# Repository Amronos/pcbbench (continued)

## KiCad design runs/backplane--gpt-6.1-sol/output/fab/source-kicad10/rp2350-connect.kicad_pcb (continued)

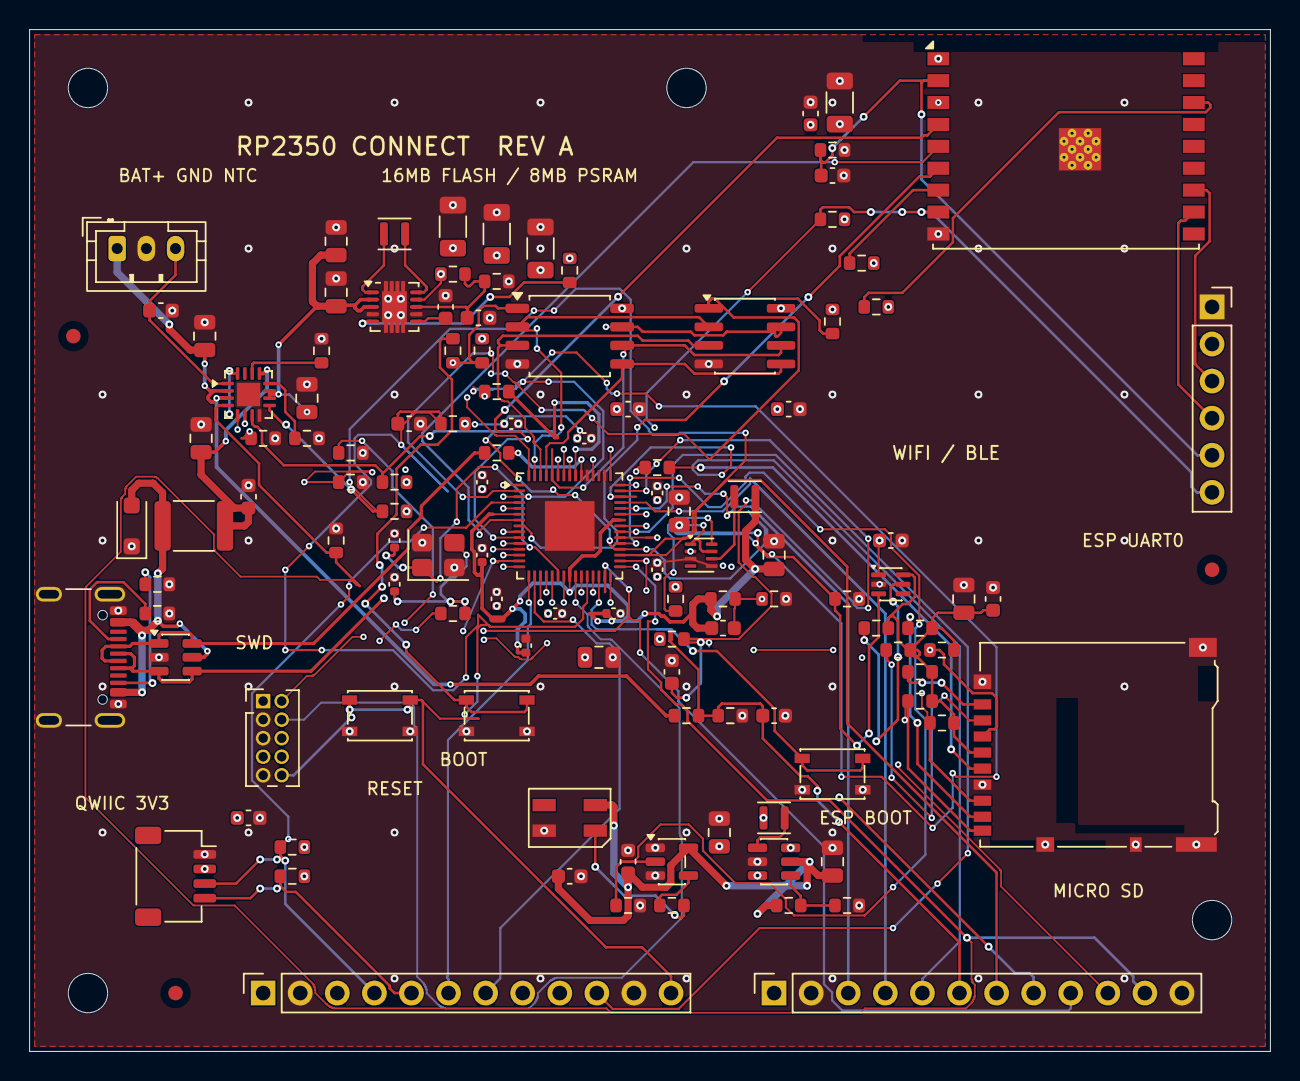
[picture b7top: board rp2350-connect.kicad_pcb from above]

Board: 6 copper layers, 85.0 x 70.0 mm, 125 parts (0 on the bottom side), 83 nets.

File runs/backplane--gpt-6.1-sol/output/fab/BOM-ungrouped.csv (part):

Reference,Value,Manufacturer,Manufacturer part number,Footprint,Fit,Notes
U1,RP2350A,Raspberry Pi,RP2350A,connect:QFN-60-1EP_7x7mm_P0.4mm_EP3.4x3.4mm,YES,Procure A2 or later silicon; do not substitute A1. Externally supplied 1.1V core; firmware sets VREG.HIZ.
U2,16MB QSPI,Winbond,W25Q128JVSIQ,connect:SOIC-8_5.3x5.3mm_P1.27mm,YES,
U3,8MB PSRAM,AP Memory,APS6404L-3SQR-SN,connect:SOIC-8_3.9x4.9mm_P1.27mm,YES,
R1,10k,Yageo,RC0603FR-0710KL,connect:R_0603_1608Metric,YES,
R2,10k,Yageo,RC0603FR-0710KL,connect:R_0603_1608Metric,YES,
C1,100n,Murata,GRM188R71C104KA01D,connect:C_0603_1608Metric,YES,
C2,100n,Murata,GRM188R71C104KA01D,connect:C_0603_1608Metric,YES,
U4,1.1V core buck,Texas Instruments,TPS62823DLCR,connect:Texas_VSON-HR-8_1.5x2mm_P0.5mm,YES,
L1,470nH,Murata,DFE201610P-R47M=P2,connect:L_Murata_DFE201610P,YES,
C3,4.7u,Murata,GRM21BR61A475KA73L,connect:C_0805_2012Metric,YES,
C4,10u,Murata,GRM21BR61A106KE19L,connect:C_0805_2012Metric,YES,
R3,83.5k,Yageo,RC0603FR-0783K5L,connect:R_0603_1608Metric,YES,
R4,100k,Yageo,RC0603FR-07100KL,connect:R_0603_1608Metric,YES,
C5,120p,Murata,GRM1885C1H121JA01D,connect:C_0603_1608Metric,YES,
R5,100k,Yageo,RC0603FR-07100KL,connect:R_0603_1608Metric,YES,
C6,100n,Murata,GRM155R71C104KA88D,connect:C_0402_1005Metric,YES,
C7,100n,Murata,GRM155R71C104KA88D,connect:C_0402_1005Metric,YES,
C8,100n,Murata,GRM155R71C104KA88D,connect:C_0402_1005Metric,YES,
C9,100n,Murata,GRM155R71C104KA88D,connect:C_0402_1005Metric,YES,
C10,100n,Murata,GRM155R71C104KA88D,connect:C_0402_1005Metric,YES,
C11,100n,Murata,GRM155R71C104KA88D,connect:C_0402_1005Metric,YES,
C12,100n,Murata,GRM155R71C104KA88D,connect:C_0402_1005Metric,YES,
C13,100n,Murata,GRM155R71C104KA88D,connect:C_0402_1005Metric,YES,
C14,100n,Murata,GRM155R71C104KA88D,connect:C_0402_1005Metric,YES,
C15,100n,Murata,GRM155R71C104KA88D,connect:C_0402_1005Metric,YES,
C16,4.7u,Murata,GRM21BR61A475KA73L,connect:C_0805_2012Metric,YES,
C17,1u,Murata,GRM188R61C105KA93D,connect:C_0603_1608Metric,YES,
R6,200,Yageo,RC0603FR-07200RL,connect:R_0603_1608Metric,YES,
Y1,12MHz CL10pF,Abracon,ABM8-272-T3,connect:Crystal_SMD_3225-4Pin_3.2x2.5mm,YES,"12MHz, CL=10pF, ESR <=50 ohms."
R7,1k,Yageo,RC0603FR-071KL,connect:R_0603_1608Metric,YES,
C18,15p,Murata,GRM1555C1H150JA01D,connect:C_0402_1005Metric,YES,
C19,15p,Murata,GRM1555C1H150JA01D,connect:C_0402_1005Metric,YES,
R8,10k,Yageo,RC0603FR-0710KL,connect:R_0603_1608Metric,YES,
C20,100n,Murata,GRM188R71C104KA01D,connect:C_0603_1608Metric,YES,
SW1,Pushbutton,C&K,PTS810SJM250SMTRLFS,connect:SW_SPST_PTS810,YES,
R9,1k,Yageo,RC0603FR-071KL,connect:R_0603_1608Metric,YES,
SW2,Pushbutton,C&K,PTS810SJM250SMTRLFS,connect:SW_SPST_PTS810,YES,
J1,USB-C,GCT,USB4105-GF-A,connect:USB_C_Receptacle_GCT_USB4105-xx-A_16P_TopMnt_Horizontal,YES,
R10,5.1k,Yageo,RC0603FR-075K1L,connect:R_0603_1608Metric,YES,
R11,5.1k,Yageo,RC0603FR-075K1L,connect:R_0603_1608Metric,YES,
U5,USB ESD,STMicroelectronics,USBLC6-2SC6,connect:SOT-23-6,YES,
R12,27,Yageo,RC0603FR-0727RL,connect:R_0603_1608Metric,YES,
R13,27,Yageo,RC0603FR-0727RL,connect:R_0603_1608Metric,YES,
F1,750mA resettable,Bourns,MF-MSMF075-2,connect:Fuse_1812_4532Metric,YES,
D1,5V TVS,Littelfuse,SMF5.0A,connect:D_SOD-123F,YES,
C21,1u,Murata,GRM188R61C105KA93D,connect:C_0603_1608Metric,YES,
U6,LiPo power-path,Texas Instruments,BQ24074RGTR,connect:VQFN-16-1EP_3x3mm_P0.5mm_EP1.6x1.6mm,YES,"External protected 1S 4.2V pack with 10k NTC. ISET=1.78k, nominal499mA. ITERM default10%."
J2,LiPo + NTC,JST,B3B-PH-K-S(LF)(SN),connect:JST_PH_B3B-PH-K_1x03_P2.00mm_Vertical,YES,
C22,10u,Murata,GRM21BR61A106KE19L,connect:C_0805_2012Metric,YES,
C23,10u,Murata,GRM21BR61A106KE19L,connect:C_0805_2012Metric,YES,
C24,10u,Murata,GRM21BR61A106KE19L,connect:C_0805_2012Metric,YES,
R14,1.78k,Yageo,RC0603FR-071K78L,connect:R_0603_1608Metric,YES,
R15,3.24k,Yageo,RC0603FR-073K24L,connect:R_0603_1608Metric,YES,
R16,39k,Yageo,RC0603FR-0739KL,connect:R_0603_1608Metric,YES,
R17,100k,Yageo,RC0603FR-07100KL,connect:R_0603_1608Metric,YES,
R18,100k,Yageo,RC0603FR-07100KL,connect:R_0603_1608Metric,YES,
R19,100k,Yageo,RC0603FR-07100KL,connect:R_0603_1608Metric,YES,
R20,10k,Yageo,RC0603FR-0710KL,connect:R_0603_1608Metric,YES,
R21,10k,Yageo,RC0603FR-0710KL,connect:R_0603_1608Metric,YES,
C25,100n,Murata,GRM188R71C104KA01D,connect:C_0603_1608Metric,YES,
U7,3.3V buck-boost,Texas Instruments,TPS63060DSCR,connect:Texas_S-PWSON-N10,YES,
L2,1uH,Murata,DFE201610P-1R0M=P2,connect:L_Murata_DFE201610P,YES,
C26,10u,Murata,GRM21BR61A106KE19L,connect:C_0805_2012Metric,YES,
C27,10u,Murata,GRM21BR61A106KE19L,connect:C_0805_2012Metric,YES,
C28,22u,Murata,GRM31CR61A226KE19L,connect:C_1206_3216Metric,YES,
C29,22u,Murata,GRM31CR61A226KE19L,connect:C_1206_3216Metric,YES,
C30,22u,Murata,GRM31CR61A226KE19L,connect:C_1206_3216Metric,YES,
C31,100n,Murata,GRM188R71C104KA01D,connect:C_0603_1608Metric,YES,
R22,560k,Yageo,RC0603FR-07560KL,connect:R_0603_1608Metric,YES,
R23,100k,Yageo,RC0603FR-07100KL,connect:R_0603_1608Metric,YES,
C32,10p,Murata,GRM1885C1H100JA01D,connect:C_0603_1608Metric,YES,
R24,100k,Yageo,RC0603FR-07100KL,connect:R_0603_1608Metric,YES,
R25,100k,Yageo,RC0603FR-07100KL,connect:R_0603_1608Metric,YES,
R26,100k,Yageo,RC0603FR-07100KL,connect:R_0603_1608Metric,YES,
C33,100n,Murata,GRM188R71C104KA01D,connect:C_0603_1608Metric,YES,
U8,Wi-Fi + BLE,Espressif Systems,ESP32-C3-WROOM-02-N4,connect:ESP32-C3-WROOM-02,YES,4MB module. Antenna projects beyond PCB north edge. Load ESP32-C3-WROOM-02 ESP-AT binary on UART0; command UART1 is GPIO6/7/5/4.
C34,22u,Murata,GRM31CR61A226KE19L,connect:C_1206_3216Metric,YES,
C35,100n,Murata,GRM188R71C104KA01D,connect:C_0603_1608Metric,YES,
R27,10k,Yageo,RC0603FR-0710KL,connect:R_0603_1608Metric,YES,
C36,100n,Murata,GRM188R71C104KA01D,connect:C_0603_1608Metric,YES,
R28,10k,Yageo,RC0603FR-0710KL,connect:R_0603_1608Metric,YES,
R29,10k,Yageo,RC0603FR-0710KL,connect:R_0603_1608Metric,YES,
R30,10k,Yageo,RC0603FR-0710KL,connect:R_0603_1608Metric,YES,
SW3,Pushbutton,C&K,PTS810SJM250SMTRLFS,connect:SW_SPST_PTS810,YES,
J3,ESP UART0,Samtec,SSQ-106-03-G-S,connect:PinSocket_1x06_P2.54mm_Vertical,YES,
J4,microSD SPI,Hirose,DM3AT-SF-PEJM5,connect:microSD_HC_Hirose_DM3AT-SF-PEJM5,YES,
R31,47k,Yageo,RC0603FR-0747KL,connect:R_0603_1608Metric,YES,
R32,47k,Yageo,RC0603FR-0747KL,connect:R_0603_1608Metric,YES,
R33,47k,Yageo,RC0603FR-0747KL,connect:R_0603_1608Metric,YES,
R34,47k,Yageo,RC0603FR-0747KL,connect:R_0603_1608Metric,YES,
R35,47k,Yageo,RC0603FR-0747KL,connect:R_0603_1608Metric,YES,
R36,47k,Yageo,RC0603FR-0747KL,connect:R_0603_1608Metric,YES,
R37,33,Yageo,RC0603FR-0733RL,connect:R_0603_1608Metric,YES,
C37,10u,Murata,GRM21BR61A106KE19L,connect:C_0805_2012Metric,YES,
C38,100n,Murata,GRM188R71C104KA01D,connect:C_0603_1608Metric,YES,
J5,Qwiic / STEMMA QT,JST,SM04B-SRSS-TB(LF)(SN),connect:JST_SH_SM04B-SRSS-TB_1x04-1MP_P1.00mm_Horizontal,YES,
R38,4.7k,Yageo,RC0603FR-074K7L,connect:R_0603_1608Metric,YES,
R39,4.7k,Yageo,RC0603FR-074K7L,connect:R_0603_1608Metric,YES,
C39,100n,Murata,GRM188R71C104KA01D,connect:C_0603_1608Metric,YES,
U9,5V LED boost,Microchip,MCP1640T-I/CHY,connect:SOT-23-6_LED,YES,
L3,2.2uH,Murata,DFE201610P-2R2M=P2,connect:L_Murata_DFE201610P,YES,
C40,4.7u,Murata,GRM21BR61A475KA73L,connect:C_0805_2012Metric,YES,
C41,10u,Murata,GRM21BR61A106KE19L,connect:C_0805_2012Metric,YES,
R40,976k,Yageo,RC0603FR-07976KL,connect:R_0603_1608Metric,YES,
R41,309k,Yageo,RC0603FR-07309KL,connect:R_0603_1608Metric,YES,
U10,LED level buffer,Texas Instruments,SN74AHCT1G125DBVR,connect:SOT-23-5,YES,
C42,100n,Murata,GRM188R71C104KA01D,connect:C_0603_1608Metric,YES,
R42,330,Yageo,RC0603FR-07330RL,connect:R_0603_1608Metric,YES,
R43,100k,Yageo,RC0603FR-07100KL,connect:R_0603_1608Metric,YES,
D2,Addressable RGB,OPSCO Optoelectronics,SK6812MINI,connect:LED_SK6812MINI_PLCC4_3.5x3.5mm_P1.75mm,YES,"5V supply, GRB data at800kHz; recommended brightness/current cap in firmware."
C43,100n,Murata,GRM188R71C104KA01D,connect:C_0603_1608Metric,YES,
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
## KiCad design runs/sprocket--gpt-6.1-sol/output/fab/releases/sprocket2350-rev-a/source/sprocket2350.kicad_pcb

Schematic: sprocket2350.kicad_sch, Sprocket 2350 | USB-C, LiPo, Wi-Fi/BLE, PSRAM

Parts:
C1, C2, C9, C10, C11, C12, C13, C14, C15, C16, C17, C18, C19, C25, C28, C31, C34, C35: 100 nF; C_0603_1608Metric; MPN GRM188R71C104KA01D
C3, C4: 15 pF; C_0603_1608Metric; MPN GRM1885C1H150JA01D
C5, C7, C8: 4.7 µF; C_0805_2012Metric; MPN GRM21BR71A475KA73L
C6: 22 µF; C_0603_1608Metric; MPN GRM188R61A226ME15D
C20: 100 nF; C_0201_0603Metric; MPN GRM033Z71C104KE14D
C21, C29: 1 µF; C_0603_1608Metric; MPN GRM188R71C105KA12D
C22, C23, C24, C30, C33: 10 µF; C_0805_2012Metric; MPN GRM21BC71E106ME11L
C26, C27, C32: 22 µF; C_1206_3216Metric; MPN GRM31CR61A226KE19L
D1: RGB V6; LED_WS2812B_PLCC4_5.0x5.0mm_P3.2mm; MPN WS2812B-V6
FID1, FID2, FID3: Fiducial; Fiducial_1mm_Mask2mm; MPN COPPER-FIDUCIAL
H1, H2, H3: M2.5; MountingHole_2.7mm_M2.5; MPN NPTH-2.7MM
J1: USB-C; USB_C_Receptacle_GCT_USB4105-xx-A_16P_TopMnt_Horizontal; MPN USB4105-GF-A
J2: LiPo; JST_PH_S2B-PH-SM4-TB_1x02-1MP_P2.00mm_Horizontal; MPN S2B-PH-SM4-TB(LF)(SN)
J3: Radio UART; PinHeader_1x04_P2.54mm_Vertical; MPN TSW-104-07-G-S
J4: microSD; microSD_HC_Hirose_DM3AT-SF-PEJM5; MPN DM3AT-SF-PEJM5
J5: Qwiic / STEMMA QT; JST_SH_BM04B-SRSS-TB_1x04-1MP_P1.00mm_Vertical; MPN BM04B-SRSS-TB(LF)(SN)
J6: GPIO; PinHeader_2x10_P2.54mm_Vertical; MPN TSW-110-07-G-D
J7: SWD; PinHeader_1x04_P2.54mm_Vertical; MPN TSW-104-07-G-S
L1: 3.3 µH; L_Abracon_AOTA-B201610S; MPN AOTA-B201610S3R3-101-T
L2: 2.2 µH; L_Coilcraft_XxL4020; MPN XFL4020-222MEC
R1, R4, R13, R16, R17, R18, R19, R23, R24, R25, R26, R27, R28, R29, R30, R31: 10 kΩ; R_0603_1608Metric; MPN RC0603FR-0710KL
R2: 1.8 kΩ; R_0603_1608Metric; MPN RC0603FR-071K8L
R3, R5, R35: 1 kΩ; R_0603_1608Metric; MPN RC0603FR-071KL
R6: 33 Ω; R_0603_1608Metric; MPN RC0603FR-0733RL
R7, R8, R32, R33: 5.1 kΩ; R_0603_1608Metric; MPN RC0603FR-075K1L
R9, R10: 27 Ω; R_0603_1608Metric; MPN RC0603FR-0727RL
R11: 8.66 kΩ; R_0603_1608Metric; MPN RC0603FR-078K66L
R12: 3.48 kΩ; R_0603_1608Metric; MPN RC0603FR-073K48L
R14: 68.1 kΩ; R_0603_1608Metric; MPN RC0603FR-0768K1L
R20, R21: 3.3 kΩ; R_0603_1608Metric; MPN RC0603FR-073K3L
R22: 100 kΩ; R_0603_1608Metric; MPN RC0603FR-07100KL
R34: 330 Ω; R_0603_1608Metric; MPN RC0603FR-07330RL
R36: 100 Ω; R_0603_1608Metric; MPN RC0603FR-07100RL
SW1: BOOT; SW_SPST_TL3342; MPN TL3342F160QG
SW2: RESET; SW_SPST_TL3342; MPN TL3342F160QG
SW3: RADIO BOOT; SW_SPST_TL3342; MPN TL3342F160QG
TP1: VBUS; TestPoint_Pad_D1.0mm; MPN COPPER-TESTPOINT
TP2: SYS; TestPoint_Pad_D1.0mm; MPN COPPER-TESTPOINT
TP3: +3V3; TestPoint_Pad_D1.0mm; MPN COPPER-TESTPOINT
TP4: GND; TestPoint_Pad_D1.0mm; MPN COPPER-TESTPOINT
TP5: BAT; TestPoint_Pad_D1.0mm; MPN COPPER-TESTPOINT
TP6: CHG_N; TestPoint_Pad_D1.0mm; MPN COPPER-TESTPOINT
TP7: USB_PGOOD_N; TestPoint_Pad_D1.0mm; MPN COPPER-TESTPOINT
TP8: CORE_1V1; TestPoint_Pad_D1.0mm; MPN COPPER-TESTPOINT
U1: RP2350A; QFN-60-1EP_7x7mm_P0.4mm_EP3.4x3.4mm; MPN RP2350A
U2: 16 MB flash; SOIC-8_5.3x5.3mm_P1.27mm; MPN W25Q128JVSIQ
U3: 8 MB PSRAM; SOIC-8_3.9x4.9mm_P1.27mm; MPN APS6404L-3SQR-SN
U4: USB ESD; SOT-23-6; MPN USBLC6-2SC6
U5: Power-path charger; VQFN-16-1EP_3x3mm_P0.5mm_EP1.6x1.6mm; MPN BQ24074RGTR
U6: 3.3 V buck-boost; Texas_DRC0010J; MPN TPS63001DRCR
U7: Wi-Fi + BLE; ESP32-C3-WROOM-02; MPN ESP32-C3-WROOM-02-N4
U8: Battery voltage / SOC; TDFN-8-1EP_2x2mm_P0.5mm_EP0.8x1.2mm; MPN MAX17048G+T10
Y1: 12 MHz; Crystal_SMD_3225-4Pin_3.2x2.5mm; MPN ABM8-272-T3

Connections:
/+3V3: C1.1, C2.1, C6.1, C9.1, C10.1, C11.1, C12.1, C13.1, C14.1, C15.1, C16.1, C17.1, C26.1, C27.1, C30.1, C31.1, C32.1, C33.1, C34.1, C35.1, D1.1 (VDD), J4.4 (VDD), J5.2, J6.1, J6.19, J7.1, R1.1, R2.1, R4.1, R6.1, R17.1, R18.1, R19.1, R20.1, R21.1, R23.1, R24.1, R25.1, R26.1, R27.1, R28.1, R29.1, R30.1, R31.1, R32.1, R33.1, TP3.1 (1_1), U1.1 (IOVDD), U1.11 (IOVDD), U1.20 (IOVDD), U1.30 (IOVDD), U1.38 (IOVDD), U1.44 (ADC_AVDD), U1.45 (IOVDD), U1.49 (VREG_VIN), U1.53 (USB_OTP_VDD), U1.54 (QSPI_IOVDD), U2.8 (VCC), U3.8 (VDD), U6.1 (VOUT), U6.10 (FB), U7.1 (3V3)
/ADC0: J6.5, U1.40 (GPIO26/ADC0)
/ADC1: J6.15, U1.41 (GPIO27/ADC1)
/ADC2: J6.16, U1.42 (GPIO28/ADC2)
/ADC3: J6.17, U1.43 (GPIO29/ADC3)
/BAT: C22.1, C28.1, J2.2, TP5.1 (1_1), U5.2 (BAT), U5.3 (BAT), U8.2 (CELL), U8.3 (VDD)
/BAT_TS: R13.1, U5.1 (TS)
/BOOT_SWITCH: R3.2, SW1.1
/BUCK_L1: L2.1, U6.4 (L1)
/BUCK_L2: L2.2, U6.2 (L2)
/BUCK_VINA: C25.1, R36.2, U6.8 (VINA)
/CC1: J1.A5 (CC1), R7.1
/CC2: J1.B5 (CC2), R8.1
/CHARGE_DISABLE: R17.2, U1.15 (GPIO11), U5.4 (~CE)
/CHG_ILIM: R12.1, U5.12 (ILIM)
/CHG_ISET: R11.1, U5.16 (ISET)
/CHG_N: R19.2, TP6.1 (1_1), U5.9 (~CHG)
/CHG_TMR: R14.1, U5.14 (TMR)
/CORE_1V1: C7.1, C8.1, C18.1, C19.1, C20.1, L1.1, TP8.1 (1_1), U1.6 (DVDD), U1.23 (DVDD), U1.39 (DVDD), U1.50 (VREG_FB)
/FLASH_CS: R1.2, R3.1, U1.60 (~QSPI_SS), U2.1 (~CS)
/GAUGE_SCL: J6.10, R21.2, U1.33 (GPIO21), U8.7 (SCL)
/GAUGE_SDA: J6.9, R20.2, U1.32 (GPIO20), U8.8 (SDA)
/GND: C1.2, C2.2, C3.2, C4.2, C5.2, C6.2, C7.2, C8.2, C9.2, C10.2, C11.2, C12.2, C13.2, C14.2, C15.2, C16.2, C17.2, C18.2, C19.2, C20.2, C21.2, C22.2, C23.2, C24.2, C25.2, C26.2, C27.2, C28.2, C29.2, C30.2, C31.2, C32.2, C33.2, C34.2, C35.2, D1.3 (VSS), J1.A1 (GND), J1.A12 (GND), J1.B1 (GND), J1.B12 (GND), J1.SH (SHIELD), J2.1, J3.1, J4.6 (VSS), J4.10 (DET_A), J4.SH (SHIELD), J5.1, J6.2, J6.20, J7.3, R7.2, R8.2, R11.2, R12.2, R13.2, R14.2, R16.2, R22.2, SW1.2, SW2.2, SW3.2, TP4.1 (1_1), U1.47 (VREG_PGND), U1.61 (GND), U2.4 (GND), U3.4 (VSS), U4.2 (GND), U5.5 (EN2), U5.8 (VSS), U5.17 (VSS), U6.3 (PGND), U6.7 (PS/SYNC), U6.9 (GND), U6.11 (PGND), U7.9 (GND), U7.19 (GND), U8.1 (CTG), U8.4 (GND), U8.6 (QSTRT), U8.9 (EP), Y1.2 (G), Y1.4 (G)
/GPIO1: J6.3, U1.3 (GPIO1)
/GPIO17: J6.6, U1.28 (GPIO17)
/GPIO18: J6.7, U1.29 (GPIO18)
/GPIO19: J6.8, U1.31 (GPIO19)
/GPIO22: J6.11, U1.34 (GPIO22)
/GPIO23: J6.12, U1.35 (GPIO23)
/GPIO24: J6.13, U1.36 (GPIO24)
/GPIO25: J6.14, U1.37 (GPIO25)
/I2C_SCL: J5.4, R33.2, U1.5 (GPIO3)
/I2C_SDA: J5.3, R32.2, U1.4 (GPIO2)
/MCU_USB_N: R10.2, U1.51 (USB_DM)
/MCU_USB_P: R9.2, U1.52 (USB_DP)
/PROG_RX: J3.3, U7.11 (IO20/RXD)
/PROG_TX: J3.2, U7.12 (IO21/TXD)
/PSRAM_CS: R2.2, U1.2 (GPIO0), U3.1 (~CE)
/QSPI_CLK: U1.56 (QSPI_SCLK), U2.6 (CLK), U3.6 (SCLK)
/QSPI_D0: U1.57 (QSPI_SD0), U2.5 (DI/IO_{0}), U3.5 (SI/SIO0)
/QSPI_D1: U1.59 (QSPI_SD1), U2.2 (DO/IO_{1}), U3.2 (SO/SIO1)
/QSPI_D2: U1.58 (QSPI_SD2), U2.3 (~WP/IO_{2}), U3.3 (SIO2)
/QSPI_D3: U1.55 (QSPI_SD3), U2.7 (~HOLD/~RESET/IO_{3}), U3.7 (SIO3)
/RADIO_BOOT: J6.4, R24.2, SW3.1, U7.8 (IO9)
/RADIO_CTRL: R35.1, U1.27 (GPIO16)
/RADIO_EN: C29.1, J3.4, R22.1, R35.2, U7.2 (EN)
/RADIO_IO2: R25.2, U7.16 (IO2)
/RADIO_IO8: R23.2, U7.7 (IO8)
/RGB_DATA: R34.1, U1.13 (GPIO9)
/RGB_DIN: D1.4 (DIN), R34.2
/RUN: J6.18, R4.2, SW2.1, U1.26 (RUN)
/SD_CLK: J4.5 (CLK), U1.9 (GPIO6)
/SD_CS: J4.2 (DAT3/CD), R26.2, U1.8 (GPIO5)
/SD_DAT1: J4.8 (DAT1), R29.2
/SD_DAT2: J4.1 (DAT2), R30.2
/SD_DETECT: J4.9 (DET_B), R31.2, U1.12 (GPIO8)
/SD_MISO: J4.7 (DAT0), R28.2, U1.7 (GPIO4)
/SD_MOSI: J4.3 (CMD), R27.2, U1.10 (GPIO7)
/SWCLK: J7.4, U1.24 (SWCLK)
/SWDIO: J7.2, U1.25 (SWDIO)
/SYS: C23.1, C24.1, R36.1, TP2.1 (1_1), U5.10 (OUT), U5.11 (OUT), U6.5 (VIN), U6.6 (EN)
/UART_CTS: U1.18 (GPIO14), U7.3 (IO4)
/UART_RTS: U1.19 (GPIO15), U7.4 (IO5)
/UART_RX: U1.17 (GPIO13), U7.6 (IO7)
/UART_TX: U1.16 (GPIO12), U7.5 (IO6)
/USB_500_EN: R16.1, U1.14 (GPIO10), U5.6 (EN1)
/USB_D_N: J1.A7 (D-), J1.B7 (D-), R10.1, U4.1 (I/O1), U4.6 (I/O1)
/USB_D_P: J1.A6 (D+), J1.B6 (D+), R9.1, U4.3 (I/O2), U4.4 (I/O2)
/USB_PGOOD_N: R18.2, TP7.1 (1_1), U5.7 (~PGOOD)
/VBUS: C21.1, J1.A4 (VBUS), J1.A9 (VBUS), J1.B4 (VBUS), J1.B9 (VBUS), TP1.1 (1_1), U4.5 (VBUS), U5.13 (IN)
/VREG_AVDD: C5.1, R6.2, U1.46 (VREG_AVDD)
/VREG_LX: L1.2, U1.48 (VREG_LX)
/XIN: C3.1, U1.21 (XIN), Y1.1
/XOUT: R5.1, U1.22 (XOUT)
/XTAL_OUT: C4.1, R5.2, Y1.3

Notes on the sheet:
16 MB flash + 8 MB PSRAM
GPIO / SWD / test access
Wi-Fi and Bluetooth LE companion
RP2350A and core supply
UART0 GPIO12-15 to ESP-AT command port GPIO6/7/4/5. GPIO16 controls radio EN. UART0 on J3 is for radio programming. Antenna overhangs the north board edge. Keep enclosure metal away.
Storage and sensor interfaces
USB-C device port
Qwiic: pin 1 GND, 2 3V3, 3 SDA, 4 SCL. Battery: pin 1 GND, pin 2 BAT. Verify cable polarity. External header supplies are references, never power inputs.
Firmware: GPIO0 = QMI CS1n. PSRAM must be initialised explicitly. RP2350A production stepping A4 preferred. All GPIOs are 3.3 V only.
USB/battery power and charging
USB default 100 mA, charging disabled, radio in reset. Firmware selects 500 mA and enables charging only after enumeration. Protected 1S LiPo only. TS uses fixed 10 kOhm: no pack temperature sensing.

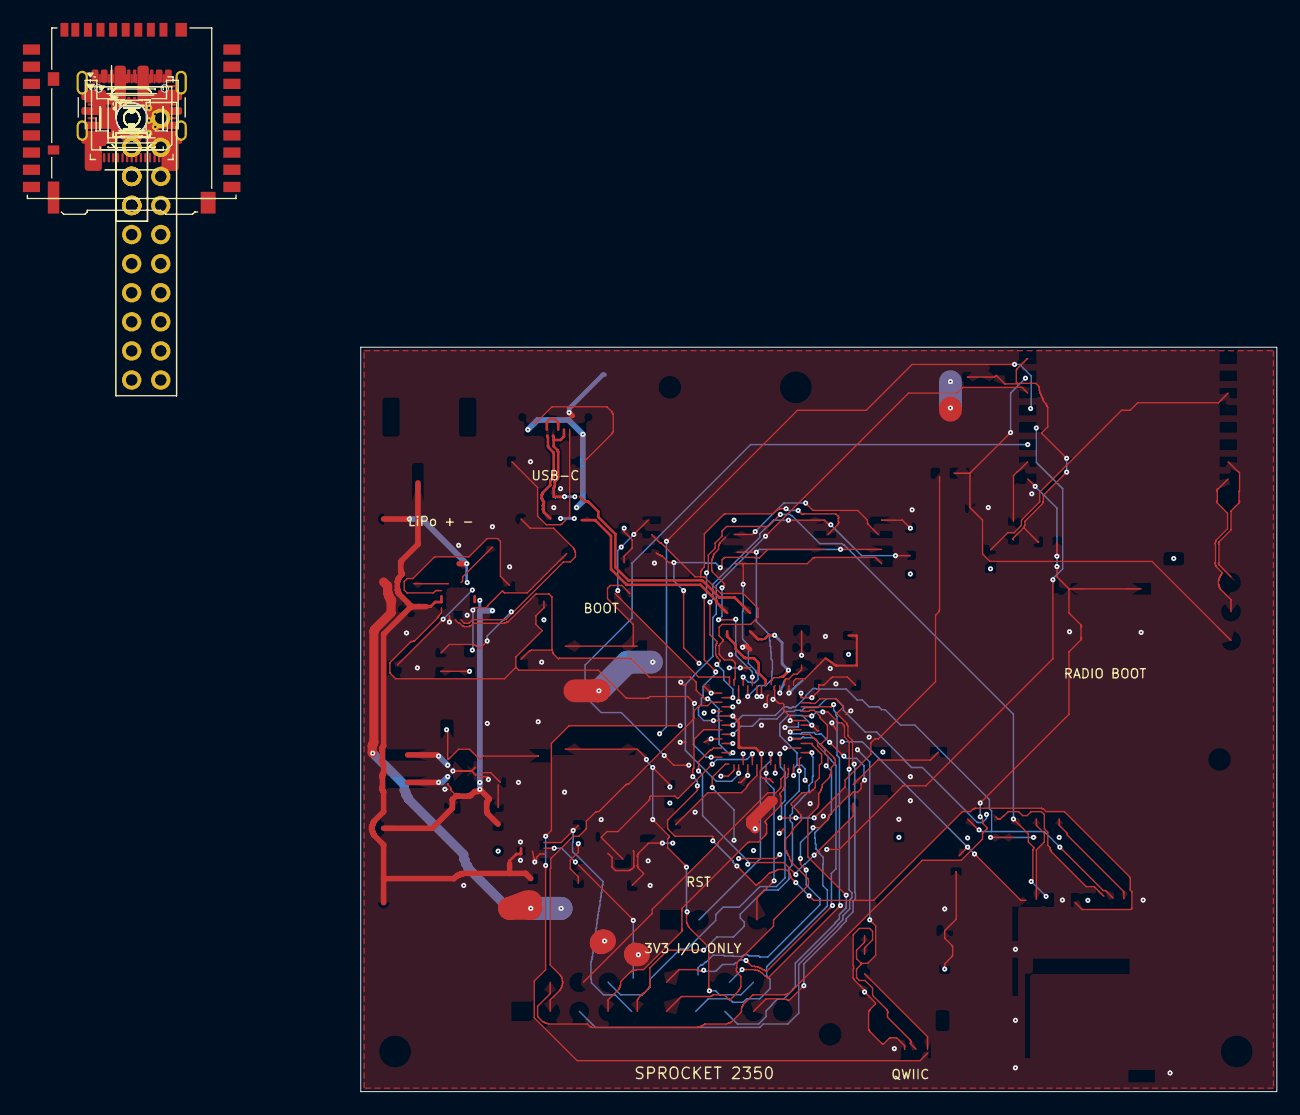
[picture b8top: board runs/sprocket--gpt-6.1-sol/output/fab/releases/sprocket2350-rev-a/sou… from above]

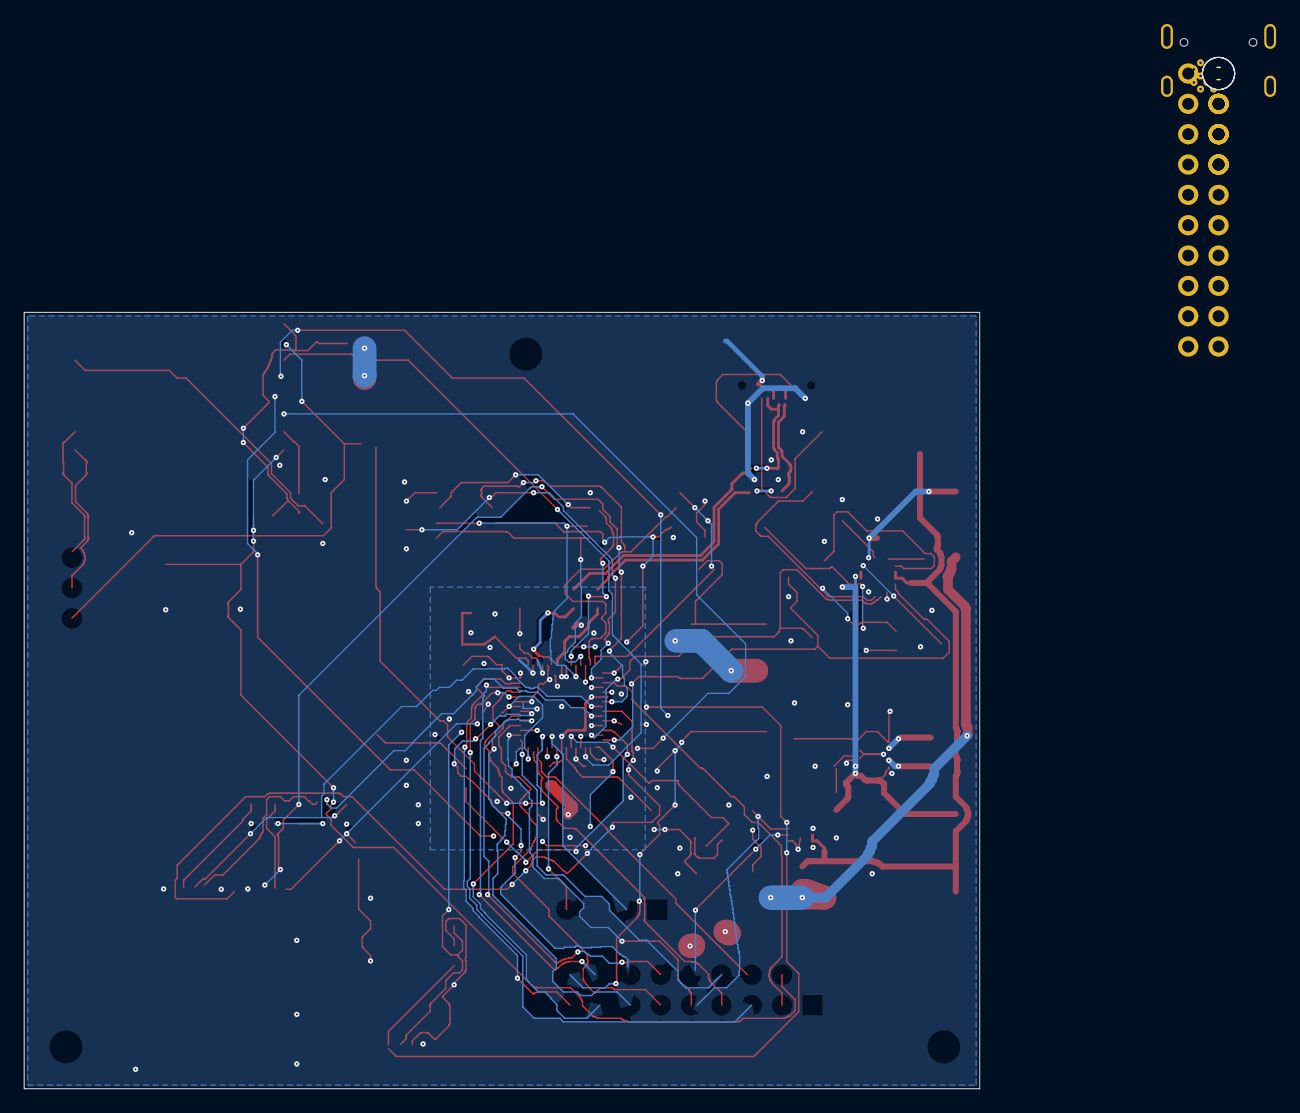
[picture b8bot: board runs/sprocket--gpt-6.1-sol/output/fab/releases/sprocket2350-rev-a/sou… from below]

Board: 4 copper layers, 80.0 x 65.0 mm, 106 parts (2 on the bottom side), 75 nets.

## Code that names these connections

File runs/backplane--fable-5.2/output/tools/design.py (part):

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       '59': 'QSPI_SD1', '60': 'QSPI_SS'}
for p in (1, 11, 20, 30, 38, 45): mcu[str(p)] = '+3V3'
for p in (6, 23, 39): mcu[str(p)] = '+1V1'
GPIO = {0: 'PSRAM_CS', 1: 'SD_CD', 2: 'SD_CLK', 3: 'SD_CMD', 4: 'SD_D0', 5: 'SD_D1', 6: 'SD_D2', 7: 'SD_D3',
        8: 'GP8', 9: 'GP9', 10: 'GP10', 11: 'GP11', 12: 'GP12', 13: 'GP13', 14: 'GP14', 15: 'GP15',
        16: 'WL_ON', 17: 'WL_CS', 18: 'WL_D', 19: 'WL_CLK', 20: 'GP20', 21: 'GP21', 22: 'GP22', 23: 'RGB_DIN',
        24: 'SDA', 25: 'SCL', 26: 'GP26_A0', 27: 'GP27_A1', 28: 'GP28_A2', 29: 'BAT_SENSE'}
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# ---------------------------------------------------------------- RM2 radio
part('U7', 'rp2350-devboard:RM2', 'RM2', 'RF_Module:RMC20452T',
     {'1': 'GND', '4': 'GND', '7': 'GND', '11': 'GND', '15': 'GND', '21': 'GND', '2': None, '19': None, '20': None,
      '3': 'WL_CLK', '5': 'WL_D', '6': 'WL_DOUT', '8': 'WL_GPIO0', '9': 'WL_CS', '10': 'WL_IRQ', '12': 'WL_ON',
      '13': 'WL_ON', '14': '+3V3', '16': '+3V3', '17': None, '18': None},
     (RX, RY, 270), (368, 55), 'RMC20452T', 'Raspberry Pi', 'C49451547',
     'Raspberry Pi Radio Module 2 (CYW43439), 2.4GHz Wi-Fi 4 + Bluetooth 5.2')
R('R25', '470R', 'WL_DOUT', 'WL_D', (57.9, 4.4, 180), (335, 76, 'h'))
R('R26', '10k', 'WL_D', 'WL_IRQ', (57.9, RY - 1.5, 0), (335, 83.5, 'h'))
R('R27', '1k', 'WL_GPIO0', 'LED_A', (57.9, RY - 4.5, 180), (335, 91, 'h'))
part('D3', 'Device:LED', 'GREEN', 'LED_SMD:LED_0603_1608Metric', {'1': 'GND', '2': 'LED_A'},
     (55.4, 6.4, 0), (372, 91), 'XL-1608SYGC-06', 'XINGLIGHT', 'C965805', 'LED yellow-green 0603, Vf 2.2V (user LED on RM2 GPIO0)')
C('C29', '100nF', '+3V3', 'GND', (56.9, 18.3, 90), (390, 80, 'v'))
C('C30', '10uF', '+3V3', 'GND', (58.2, 18.3, 90), (398, 80, 'v'))
C('C31', '100nF', '+3V3', 'GND', (58.45, 14.6, 90), (406, 80, 'v'))
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    (250, 25, 314, 95, '3V3 LDO, battery sense'),
    (318, 25, 410, 95, 'Wi-Fi / BLE (Raspberry Pi RM2)'),
    (15, 100, 195, 280, 'RP2350A, core SMPS, crystal, reset, SWD'),
    (200, 100, 298, 200, 'QSPI flash (XIP CS0) + PSRAM (XIP CS1 = GPIO0), BOOT'),
    (302, 100, 410, 200, 'microSD (SDIO 4-bit / SPI0), pull-ups: RP2350 internal'),
    (200, 204, 410, 248, 'Qwiic / STEMMA QT, RGB LED, headers (J5/J6 not populated)'),
]
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NOTES = [
    (128, 86, 'Charge current 890/R7 = 297 mA. USB input limit 500 mA (EN2=0, EN1=1 while VBUS present).'),
    (128, 90, 'TS tied to 10k (no NTC in a 2-wire pack). Safety timers and 10% termination at defaults (TMR, ITERM open).'),
    (252, 90, 'BAT_SENSE = VBAT/2 on GPIO29 / ADC3'),
    (320, 36, 'gSPI wired like Pico 2 W; pins: ON=GP16 CS=GP17 DATA=GP18 CLK=GP19'),
    (18, 262, 'SWD test pads are on the bottom side'),
    (18, 111, 'Core supply: on-chip SMPS, L1 = AOTA-B201610S3R3-101-T (polarised, dot to +1V1)'),
    (202, 111, 'GPIO0 = XIP_CS1 (PSRAM), pulled up by R19'),
    (304, 196, 'CLK=GP2 CMD=GP3 D0..D3=GP4..GP7 CD=GP1 (switch to GND)'),
    (202, 244, 'I2C0: SDA=GP24 SCL=GP25. RGB LED on GP23, powered from 3V3.'),
]
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
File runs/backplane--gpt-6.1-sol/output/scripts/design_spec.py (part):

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cap('C16','4.7u','3V3','decoupling',(139,143,0),'4.7u')
cap('C17','1u','ADC_3V3','decoupling',(144,144,90),'1u');r('R6','200','200R','3V3','ADC_3V3','decoupling',(144,142,0))
# crystal CL=10 pF, 15 pF caps plus stray capacitance, 1k drive damping.
part('Y1','Device:Crystal_GND24','12MHz CL10pF','ABM8-272-T3','Abracon',{1:'XIN',2:'GND',3:'XOUT',4:'GND'},'clock',(128,136,0),'Crystal:Crystal_SMD_3225-4Pin_3.2x2.5mm',note='12MHz, CL=10pF, ESR <=50 ohms.')
r('R7','1k','1K','XOUT_DRV','XOUT','clock',(129,140,0));cap('C18','15p','XIN','clock',(125,135,90),'15p');cap('C19','15p','XOUT','clock',(125,138,90),'15p')
r('R8','10k','10K','RUN','3V3','controls',(129,127,0));cap('C20','100n','RUN','controls',(127,127,0));sw('SW1','RUN','controls',(124,147,0));r('R9','1k','1K','FLASH_CS','BOOT_SW','controls',(129,122,90));sw('SW2','BOOT_SW','controls',(132,147,0))
# USB-C sink, USB2 data, independently terminated CCs.
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# battery ADC divider, 2:1; 21uA at4.2V and RC filtering.
r('R25','100k','100K','VBAT','VBAT_ADC','batteryadc',(145,147,0));r('R26','100k','100K','VBAT_ADC','GND','batteryadc',(148,147,0));cap('C33','100n','VBAT_ADC','batteryadc',(151,147,0))
# ESP-AT UART1, 4-wire flow control. UART0 separately exposed for programming.
esppins={1:'3V3',2:'ESP_EN',3:'ESP_AT_RTS',4:'ESP_AT_CTS',5:'ESP_AT_RX',6:'ESP_AT_TX',7:'ESP_STRAP8',8:'ESP_BOOT',9:'GND',10:None,11:'ESP_PROG_RX',12:'ESP_PROG_TX',13:None,14:None,15:None,16:'ESP_STRAP2',17:None,18:None,19:'GND'}
part('U8','RF_Module:ESP32-C3-WROOM-02','Wi-Fi + BLE','ESP32-C3-WROOM-02-N4','Espressif Systems',esppins,'radio',(171,108,0),schpos=(251.46,43.18),note='4MB module. Antenna projects beyond PCB north edge. Load ESP32-C3-WROOM-02 ESP-AT binary on UART0; command UART1 is GPIO6/7/5/4.')
cap('C34','22u','3V3','radio',(157,105,90),'22u');cap('C35','100n','3V3','radio',(159,104,90))
r('R27','10k','10K','ESP_EN','GND','radio',(159,108,0));cap('C36','100n','ESP_EN','radio',(159,110,0))
r('R28','10k','10K','ESP_BOOT','3V3','radio',(157,113,0));r('R29','10k','10K','ESP_STRAP8','3V3','radio',(157,115,0));r('R30','10k','10K','ESP_STRAP2','3V3','radio',(180,103,0));sw('SW3','ESP_BOOT','radio',(155,151,0))
part('J3','Connector_Generic:Conn_01x06','ESP UART0','SSQ-106-03-G-S','Samtec',{1:'GND',2:'3V3',3:'ESP_PROG_TX',4:'ESP_PROG_RX',5:'ESP_EN',6:'ESP_BOOT'},'radio',(181,119,0),'Connector_PinSocket_2.54mm:PinSocket_1x06_P2.54mm_Vertical')
# microSD: SPI1 24MHz maximum initial qualification target, idle pullups.
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for i,net,pos in [(31,'SD_CS',(164,142,0)),(32,'SD_MOSI',(164,144,0)),(33,'SD_MISO',(164,146,0)),(34,'SD_DAT1',(161,142,0)),(35,'SD_DAT2',(161,144,0)),(36,'SD_DET_N',(161,146,0))]:r('R'+str(i),'47k','47K',net,'3V3','sd',pos)
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part('D2','LED:SK6812MINI','Addressable RGB','SK6812MINI','OPSCO Optoelectronics',{1:None,2:'GND',3:'RGB_DIN',4:'LED_5V'},'rgb',(137,154,0),note='5V supply, GRB data at800kHz; recommended brightness/current cap in firmware.')
cap('C43','100n','LED_5V','rgb',(137,158,0))
# Fully installed GPIO sockets and keyed debug header.
part('J6','Connector_Generic:Conn_01x12','GPIO socket A','SSQ-112-03-G-S','Samtec',{1:'3V3',2:'GND',3:'GP1',4:'I2C_SDA',5:'I2C_SCL',6:'GP12',7:'GP13',8:'GP14',9:'GP15',10:'GP25',11:'GND',12:'RUN'},'expansion',(116,166,90),'Connector_PinSocket_2.54mm:PinSocket_1x12_P2.54mm_Vertical')
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part('J8','Connector_Generic:Conn_02x05_Odd_Even','SWD','FTSH-105-01-L-D-K','Samtec',{1:'3V3',2:'SWDIO',3:'GND',4:'SWCLK',5:'GND',6:None,7:None,8:None,9:'GND',10:'RUN'},'debug',(116,146,0),'Connector_PinHeader_1.27mm:PinHeader_2x05_P1.27mm_Vertical')
# microSD held off until firmware grants the USB power budget.
for c in COMP:
 if c['ref']=='U1':c['pins']['3']='SD_PWR_EN'
 if c['ref']=='J6':c['pins']['3']='SD_PWR_EN'
 if c['group']=='sd':
  c['pins']={k:('SD_3V3' if v=='3V3' else v) for k,v in c['pins'].items()}
part('U11','Power_Management:TPS22919DCK','SD power switch','TPS22919DCKR','Texas Instruments',{1:'3V3',2:'GND',3:'SD_PWR_EN',4:None,5:'SD_QOD',6:'SD_3V3'},'sd',(159,138,0),schpos=(281.94,134.62))
r('R44','100k','100K','SD_PWR_EN','GND','sd',(156,139,0));r('R45','100','100R','SD_QOD','SD_3V3','sd',(158,141,0));cap('C44','100n','3V3','sd',(159,135,0))

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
